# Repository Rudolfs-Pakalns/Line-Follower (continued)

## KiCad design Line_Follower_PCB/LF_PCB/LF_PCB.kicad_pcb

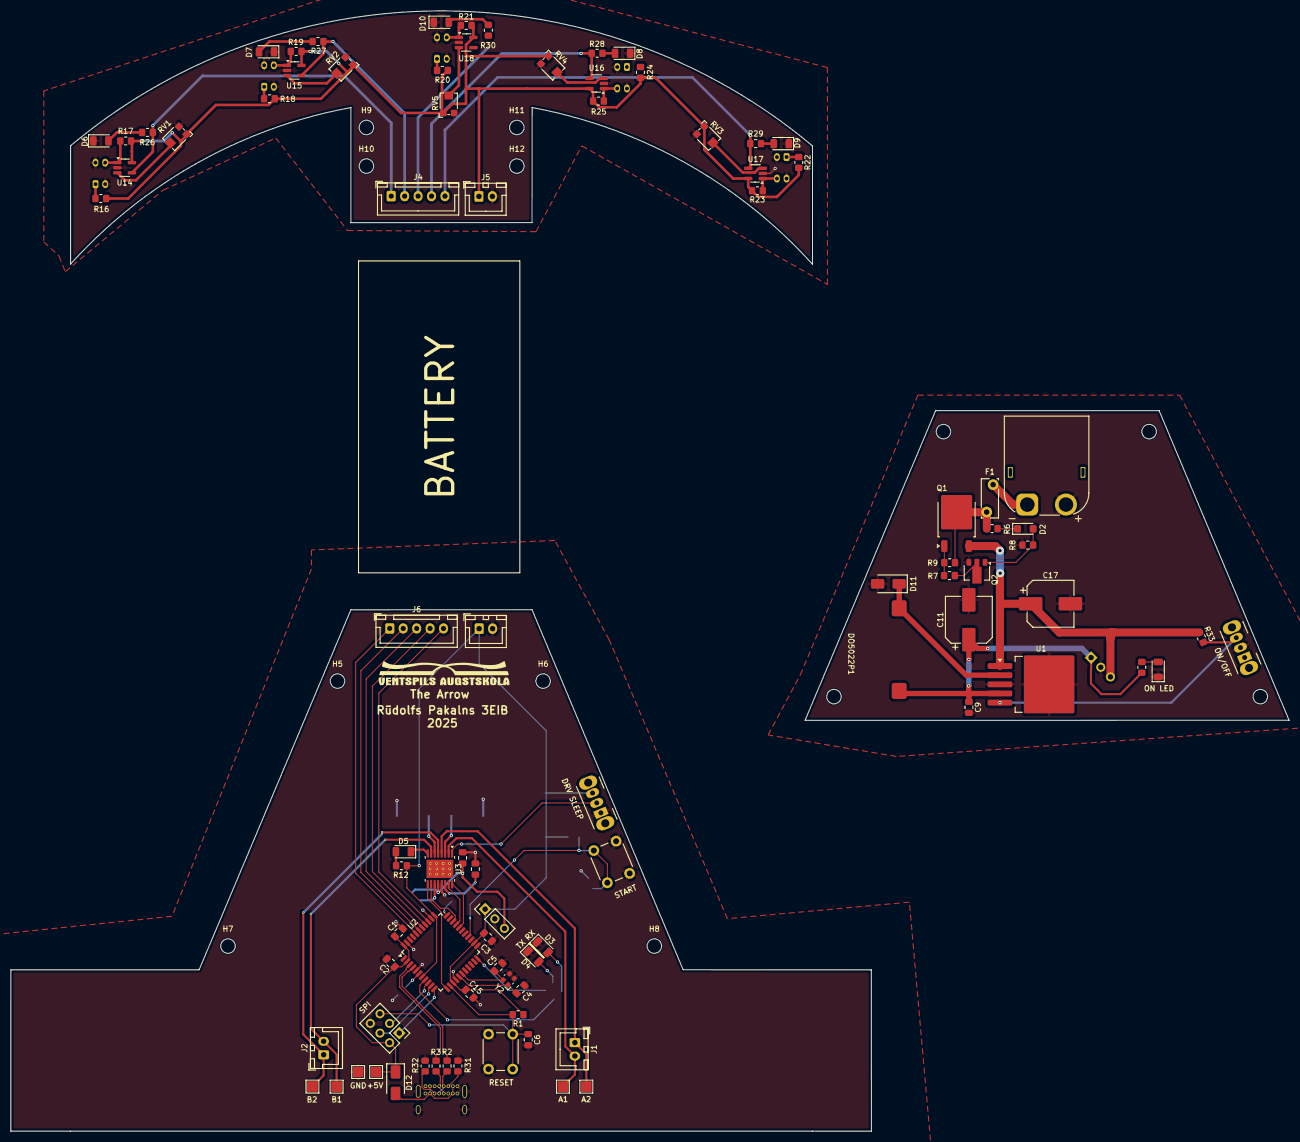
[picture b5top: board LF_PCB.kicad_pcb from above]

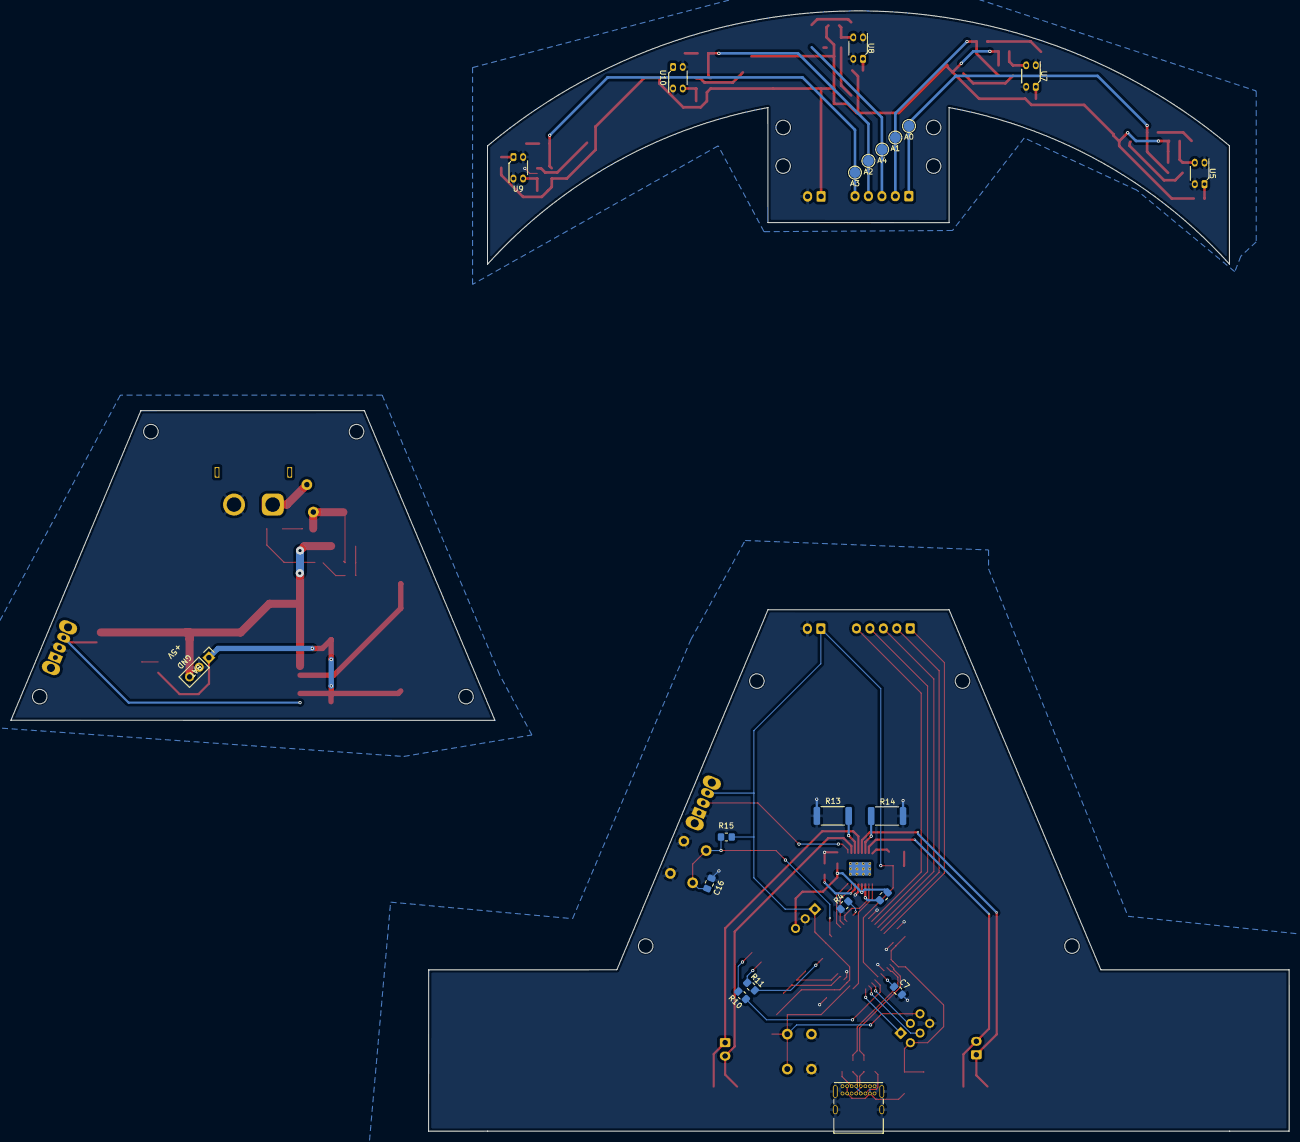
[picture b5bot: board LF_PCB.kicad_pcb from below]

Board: 2 copper layers, 237.8 x 208.4 mm, 121 parts (21 on the bottom side), 72 nets.

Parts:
A0, A1, A2, A3, A4: TestPoint; TestPoint_Pad_D2.0mm
BT1: Battery; AMASS_XT60PW-M_1x02_P7.20mm_Horizontal
C1, C2, C3, C6, C9, C15, C16: 100n; C_0805_2012Metric_Pad1.18x1.45mm_HandSolder
C4, C5: 22p; C_0805_2012Metric_Pad1.18x1.45mm_HandSolder
C7: 1u; C_0805_2012Metric_Pad1.18x1.45mm_HandSolder
C11: 220u; CP_Elec_8x10.5
C12: 10u; C_0805_2012Metric_Pad1.18x1.45mm_HandSolder
C13: 2u2; C_0805_2012Metric_Pad1.18x1.45mm_HandSolder
C14: 10n; C_0805_2012Metric_Pad1.18x1.45mm_HandSolder
C17: 470uF; CP_Elec_8x10.5
D1: ON; LED_1206_3216Metric
D2: D_Zener; D_SMF
D3: RX_LED; LED_1206_3216Metric
D4: TX_LED; LED_1206_3216Metric
D5: FAULT; LED_1206_3216Metric
D6, D7, D8, D9, D10: RED; LED_1206_3216Metric
D11, D12: D_Schottky; D_SMA
DO5022P1: 22hH; DO5022P
F1: Fuse; Fuse_Bourns_MF-RG300
H1, H2, H3, H4, H5, H6, H7, H8, H9, H10, H11, H12: MountingHole; MountingHole_2.7mm_M2.5_ISO14580
J1: MOT-A; JST_XH_B2B-XH-A_1x02_P2.50mm_Vertical
J2: MOT-B; JST_XH_B2B-XH-A_1x02_P2.50mm_Vertical
J3: USB_C_Receptacle_USB2.0_16P; USB_C_Receptacle_GCT_USB4085
J4, J6: Signals; JST_XH_B5B-XH-A_1x05_P2.50mm_Vertical
J5, J7: Power; JST_XH_B2B-XH-A_1x02_P2.50mm_Vertical
J8, J9: Conn_01x03_Pin; PinHeader_1x03_P2.54mm_Vertical
J14: SPI; PinHeader_2x03_P2.54mm_Vertical
Q1: SUD50P06-15; TO-252-2
Q2: BCX56; SOT-89-3
R1, R4, R9, R15, R33: 10k; R_0805_2012Metric_Pad1.20x1.40mm_HandSolder
R2, R3: 22; R_0805_2012Metric_Pad1.20x1.40mm_HandSolder
R5, R10, R11, R12, R26, R27, R28, R29, R30: 1k; R_0805_2012Metric_Pad1.20x1.40mm_HandSolder
R6: 130; R_0805_2012Metric_Pad1.20x1.40mm_HandSolder
R7, R16, R18, R20, R22, R24: 220; R_0805_2012Metric_Pad1.20x1.40mm_HandSolder
R8: 400; R_0805_2012Metric_Pad1.20x1.40mm_HandSolder
R13, R14: 0.2; R_2512_6332Metric
R17, R19, R21, R23, R25: 47k; R_0805_2012Metric_Pad1.20x1.40mm_HandSolder
R31, R32: 5k1; R_0805_2012Metric_Pad1.20x1.40mm_HandSolder
RV1, RV2, RV3, RV4, RV5: 10k; Potentiometer_Bourns_TC33X_Vertical
SW1: USER; SW_PUSH_6mm_H4.3mm
SW2: Sl_En; SW_Slide_SPDT_Angled_CK_OS102011MA1Q
SW3: RESET; SW_PUSH_6mm_H4.3mm
SW4: SW_Nidec_CAS-120A1; SW_Slide_SPDT_Angled_CK_OS102011MA1Q
TP5, TP6, TP7, TP8, TP9, TP10: TestPoint; TestPoint_Pad_2.0x2.0mm
U1: LM2596S-5; TO-263-5_TabPin3
U2: ATmega32U4-A; TQFP-44_10x10mm_P0.8mm
U3: DRV8833PW; HTSSOP-16-1EP_4.4x5mm_P0.65mm_EP3.4x5mm_Mask2.46x2.31mm_The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
U5, U7, U8, U9, U10: QRE1113; OnSemi_CASE100AQ
U14, U15, U16, U17, U18: MCP6001U; SOT-23-5_HandSoldering
Y2: Crystal_GND23; Crystal_SMD_Abracon_ABM10-4Pin_2.5x2.0mm

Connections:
+5V: C1.1, C2.1, C3.1, C9.1, C11.1, C15.1, D12.1 (K), DO5022P1.2, J5.1, J7.1, J8.1, J9.1, J14.2, R1.1, R5.1, R12.2, R15.1, R16.2, R17.2, R18.2, R19.2, R20.2, R21.2, R22.2, R23.2, R24.2, R25.2, RV1.1, RV2.1, RV3.1, RV4.1, RV5.1, SW2.3 (A), TP9.1, U1.4 (FB), U2.2 (UVCC), U2.7 (VBUS), U2.14 (VCC), U2.24 (AVCC), U2.34 (VCC), U2.44 (AVCC), U14.5 (V+), U15.5 (V+), U16.5 (V+), U17.5 (V+), U18.5 (V+)
/ATmega32U4/D1+: J3.A6 (D+), J3.B6 (D+), R2.2
/ATmega32U4/D1-: J3.A7 (D-), J3.B7 (D-), R3.1
/ATmega32U4/D+: R2.1, U2.4 (D+)
/ATmega32U4/D-: R3.2, U2.3 (D-)
/ATmega32U4/MISO: J14.1, U2.11 (PB3)
/ATmega32U4/MOSI: J14.4, U2.10 (PB2)
/ATmega32U4/RESET: C6.1, J14.5, R1.2, SW3.2, U2.13 (~RESET)
/ATmega32U4/RX: R10.1, U2.8 (PB0)
/ATmega32U4/SCK: J14.3, U2.9 (PB1)
/ATmega32U4/TX: R11.1, U2.22 (PD5)
/ATmega32U4/USER_BTN: C16.1, R15.2, SW1.2, U2.26 (PD6)
/ATmega32U4/XTAL1: C5.1, U2.17 (XTAL1), Y2.4
/ATmega32U4/XTAL2: C4.1, U2.16 (XTAL2), Y2.1
/Motor Driver/AOUT1: J1.2, TP5.1, U3.2 (AOUT1)
/Motor Driver/AOUT2: J1.1, TP6.1, U3.4 (AOUT2)
/Motor Driver/ASEN: R13.1, U3.3 (AISEN)
/Motor Driver/BOUT1: J2.2, TP7.1, U3.7 (BOUT1)
/Motor Driver/BOUT2: J2.1, TP8.1, U3.5 (BOUT2)
/Motor Driver/BSEN: R14.1, U3.6 (BISEN)
/Motor Driver/Sleep: SW2.2 (B), U3.1 (~SLEEP)
/Sensors/COMP1: R17.1, U5.3, U14.1 (+)
/Sensors/COMP2: R19.1, U7.3, U15.1 (+)
/Sensors/COMP3: R21.1, U8.3, U18.1 (+)
/Sensors/COMP4: R23.1, U9.3, U17.1 (+)
/Sensors/COMP5: R25.1, U10.3, U16.1 (+)
A0: A3.1, J4.5, J6.5, R29.2, U2.36 (PF7), U17.4
A1: A2.1, J4.4, J6.4, R28.2, U2.37 (PF6), U16.4
A2: A4.1, J4.3, J6.3, R30.2, U2.38 (PF5), U18.4
A3: A1.1, J4.2, J6.2, R27.2, U2.39 (PF4), U15.4
A4: A0.1, J4.1, J6.1, R26.2, U2.40 (PF1), U14.4
BAT: C12.1, C14.1, C17.1, J8.3, J9.3, Q1.3 (S), R33.1, U1.1 (VIN), U3.12 (VM)
D5: U2.31 (PC6), U3.10 (BIN2)
D9: U2.29 (PB5), U3.16 (AIN1)
D10: U2.30 (PB6), U3.15 (AIN2)
D11: U2.12 (PB7), U3.9 (BIN1)
GND: BT1.2 (-), C1.2, C2.2, C3.2, C4.2, C5.2, C6.2, C7.2, C9.2, C11.2, C12.2, C13.1, C15.2, C16.2, C17.2, D1.1 (K), D3.1 (K), D4.1 (K), D6.1 (K), D7.1 (K), D8.1 (K), D9.1 (K), D10.1 (K), D11.2 (A), J3.A1 (GND), J3.A12 (GND), J3.B1 (GND), J3.B12 (GND), J3.S1 (SHIELD), J5.2, J7.2, J8.2, J9.2, J14.6, Q2.3 (E), R4.2, R8.1, R13.2, R14.2, R31.2, R32.2, RV1.3, RV2.3, RV3.3, RV4.3, RV5.3, SW1.1, SW2.1 (C), SW3.1, SW4.2 (B), TP10.1, U1.3 (GND), U2.5 (UGND), U2.15 (GND), U2.23 (GND), U2.35 (GND), U2.43 (GND), U3.13 (GND), U5.2 (K), U5.4, U7.2 (K), U7.4, U8.2 (K), U8.4, U9.2 (K), U9.4, U10.2 (K), U10.4, U14.2 (V-), U15.2 (V-), U16.2 (V-), U17.2 (V-), U18.2 (V-), Y2.2, Y2.3
unnamed: BT1.1 (+), F1.1
unnamed: D1.2 (A), R5.2
unnamed: D2.2 (A), Q2.1 (B), R8.2
unnamed: D2.1 (K), R6.1
unnamed: D3.2 (A), R10.2
unnamed: D4.2 (A), R11.2
unnamed: D5.2 (A), R12.1
unnamed: D5.1 (K), U3.8 (~FAULT)
unnamed: D6.2 (A), R26.1
unnamed: D7.2 (A), R27.1
unnamed: D8.2 (A), R28.1
unnamed: D9.2 (A), R29.1
unnamed: D10.2 (A), R30.1
unnamed: D11.1 (K), DO5022P1.1, U1.2 (OUT)
unnamed: D12.2 (A), J3.A4 (VBUS), J3.A9 (VBUS), J3.B4 (VBUS), J3.B9 (VBUS)
unnamed: J3.A5 (CC1), R31.1
unnamed: J3.B5 (CC2), R32.1
unnamed: F1.2, Q1.2 (D), R6.2, R9.2
unnamed: Q1.1 (G), R7.2, R9.1
unnamed: Q2.2 (C), R7.1
unnamed: R33.2, SW4.3 (A), U1.5 (~ON/OFF)
unnamed: C7.1, U2.6 (UCAP)
unnamed: R4.1, U2.33 (~HWB/PE2)
unnamed: C14.2, U3.11 (VCP)
unnamed: C13.2, U3.14 (VINT)
unnamed: R16.1, U5.1 (A)
unnamed: R18.1, U7.1 (A)
unnamed: R20.1, U8.1 (A)
unnamed: R22.1, U9.1 (A)
unnamed: R24.1, U10.1 (A)
unnamed: RV1.2, U14.3 (-)
unnamed: RV2.2, U15.3 (-)
unnamed: RV4.2, U16.3 (-)
unnamed: RV3.2, U17.3 (-)
unnamed: RV5.2, U18.3 (-)

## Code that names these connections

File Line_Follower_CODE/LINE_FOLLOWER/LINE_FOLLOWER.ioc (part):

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Mcu.Name=STM32G071G(6-8-B)Ux
Mcu.Package=UFQFPN28
Mcu.UserName=STM32G071GBUx
PA11\ [PA9].GPIOParameters=GPIO_Label
PA11\ [PA9].GPIO_Label=BIN1
PA11\ [PA9].Signal=S_TIM1_CH4
PA13.Mode=Serial_Wire
PA13.Signal=SYS_SWDIO
PA14-BOOT0.Mode=Serial_Wire
PA14-BOOT0.Signal=SYS_SWCLK
PA2.Mode=Asynchronous
PA2.Signal=USART2_TX
PA3.Mode=Asynchronous
PA3.Signal=USART2_RX
PA8.GPIOParameters=GPIO_Label
PA8.GPIO_Label=AIN2
PA8.Signal=S_TIM1_CH1
PB0.GPIOParameters=GPIO_Label
PB0.GPIO_Label=nSleep
PB0.Signal=GPIO_Output
PB1.GPIOParameters=GPIO_Label
PB1.GPIO_Label=AIN1
PB1.Signal=S_TIM3_CH4
PB4.GPIOParameters=GPIO_Label
PB4.GPIO_Label=Sensor_1
PB4.Signal=GPIO_Input
PB5.GPIOParameters=GPIO_Label
PB5.GPIO_Label=Sensor_2
PB5.Signal=GPIO_Input
PB6.GPIOParameters=GPIO_Label
PB6.GPIO_Label=Sensor_3
PB6.Signal=GPIO_Input
PB7.GPIOParameters=GPIO_Label
PB7.GPIO_Label=Sensor_4
PB7.Signal=GPIO_Input
PB8.GPIOParameters=GPIO_Label
PB8.GPIO_Label=Sensor_5
PB8.Signal=GPIO_Input
PC14-OSC32_IN\ (PC14).GPIOParameters=GPIO_Label
PC14-OSC32_IN\ (PC14).GPIO_Label=Start
PC14-OSC32_IN\ (PC14).Signal=GPIO_Input
PC6.GPIOParameters=GPIO_Label
PC6.GPIO_Label=BIN2
PC6.Signal=S_TIM3_CH1
RCC.HSE_VALUE=8000000
RCC.SYSCLKFreq_VALUE=16000000
board=custom

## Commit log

2025-12-15 Initial commit; added project
2025-12-15 made schematic; missing DRV8833
2025-12-15 Added a bunch of shit
2025-12-16 Started PCB
2025-12-17 Completed schematic
2025-12-17 Added code
2025-12-19 Made PCB
2025-12-20 seperated PCBs into 3 seperate files and updated README
2026-01-05 more stuff
2026-01-12 Updated schematic
2026-01-13 Updates and stuff
2026-02-05 added new 3d design
2026-02-06 Updated code
2026-03-17 Added somewhat ok code
2026-03-19 Edit: updated RF schematic
2026-03-19 Edit: Updated code
2026-05-23 first commit; added project
2026-05-24 Updated code with test funcs
2026-05-24 added full functionality in code
2026-05-24 added command to set base speed
